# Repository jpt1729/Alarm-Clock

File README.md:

# Alarm-Clock

Custom built alarm clock. I was partly inspired by this https://busy.bar/. I also just wanted ot make a cool custom project and right now I only have an Alexa next to my bed so I can't actually see the current time, but with this it should both wake me up and it should tell me the time :) 

What this basically is its an ESP32 controlled alarm clock that connects to Wifi has a 1.9" LCD display and a snooze bar. It serves as a clock and an alarm (as of now, but I want to program it a bit more in the future!)

When I first learned about making PCBs this (along with a keyboard [which I already made!]) was one of the projects I wanted to try my hand at so I am happy I got to do it!

The plan to make the case a bit easier to print is to print the top part out and then the bottom part out and connect the two with a soldering iron. This will use a lot less plastic (if not I will basically be printing a solid block of plastic).

# Photos

# BOM

| Item | Quantity Used | Quantity Purchased | Designator | Part Number / Description | Link | Cost |
|------|--------------|-------------------|------------|--------------------------|------|------|
| Case | 1 | | | Custom Case | | |
| PCB | 1 | 5 | | Custom PCB | | $8.90 |
| JST Connector | 4 | 5 | | JST-XH-A 5 | [LCSC](https://lcsc.com/product-detail/Wire-To-Board-Connector_JST-B5B-XH-A-LF-SN_C157991.html) | $0.42 |
| JST Connector | 2 | 5 | | JST-XH-A 8 | [LCSC](https://lcsc.com/product-detail/Wire-To-Board-Connector_JST-B8B-XH-A-LF-SN_C157972.html) | $0.66 |
| MCU | 1 | 1 | | ESP-32-S3-MINI-1 | [LCSC](https://lcsc.com/product-detail/WiFi-Modules_Espressif-Systems-ESP32-S3-MINI-1-N8_C2913206.html) | $5.11 |
| Buzzer | 2 | 5 | | TMB12A05 | [LCSC](https://lcsc.com/product-detail/Buzzers_Jiangsu-Huaneng-Elec-TMB12A05_C96093.html) | $0.90 |
| Capacitor | 1 | 100 | C1 | 0603 1uF (100nF) | [LCSC](https://lcsc.com/product-detail/image/CC0603KRX7R9BB104_C14663.html) | $0.24 |
| USB Connector | 1 | 1 | J1 | USB-C USB4105-GF-A | [LCSC](https://lcsc.com/product-detail/USB-Connectors_Global-Connector-Technology-USB4105-GF-A_C3020560.html) | $1.16 |
| LCD Display | 1 | 10 | | 1.9" LCD | [AliExpress](https://www.aliexpress.us/item/3256807182983606.html) | $3.25 |
| Diodes | 2 | 10 | | 40V 200mA NPN TO-92 | [LCSC](https://lcsc.com/product-detail/image/2N3904X_C5156722.html) | $0.38 |
| Resistor | 1 | 100 | R1 | 10k Ohm 0603 | [LCSC](https://lcsc.com/product-detail/image/RC0603FR-0710KL_C98220.html) | $0.11 |
| Resistor | 2 | 100 | R2, R3 | 5.1k Ohm 0603 | [LCSC](https://lcsc.com/product-detail/image/RC0603FR-075K1L_C105580.html) | $0.12 |
| Resistor | 2 | 100 | R4, R5 | 1k Ohm 0603 | [LCSC](https://lcsc.com/product-detail/Chip-Resistor-Surface-Mount_YAGEO-RC0603FR-071KL_C22548.html) | $0.11 |
| Switch | 1 | 10 | SW1 | Gateron Low Profile | [AliExpress](https://www.aliexpress.us/item/3256808635477539.html) | $5.79 |
| Encoder | 1 | 5 | ENC1 | EC11 Rotary Encoder | [AliExpress](https://www.aliexpress.us/item/3256801237549169.html) | $0.99 |
| Voltage Regulator | 1 | 5 | U1 | AMS1117-3.3 | [LCSC](https://lcsc.com/product-detail/Voltage-Regulators-Linear-Low-Drop-Out-LDO-Regulators_Advanced-Monolithic-Systems-AMS1117-3-3_C6186.html) | $0.87 |
| SXH-001T-P0.6 | | 100 | | Terminal pin (x100) | [LCSC](https://lcsc.com/product-detail/Housing-Contact_JST-SXH-001T-P0-6_C140573.html) | $1.08 |
| XHP-5 | | 20 | | 5-pin housing (x20) | [LCSC](https://lcsc.com/product-detail/Housings-Wire-To-Board-Wire-To-Wire_JST-XHP-5_C144404.html) | $0.46 |
| XHP-8 | | 20 | | 8-pin housing (x20) | [LCSC](https://lcsc.com/product-detail/Housings-Wire-To-Board-Wire-To-Wire_JST-XHP-8_C144407.html) | $0.65 |
| Connector Kit (Amazon) | | | | SXH-001T-P0.6, XHP-5, XHP-8 Assortment | [Amazon](https://a.co/d/gTI01NR) | $6.97 |
| Shipping JLC PCB | | | | | | $22.73 |
| Shipping LCSC | | | | | | $17.39 |
| Shipping AliExpress | | | | | | $0.00 |
| Hotplate | 1 | 1 | | Soldering Hotplate | [AliExpress](https://www.aliexpress.us/item/3256806325004979.html) | $20.05 |
| **Total** | | | | | | **$77.72** |

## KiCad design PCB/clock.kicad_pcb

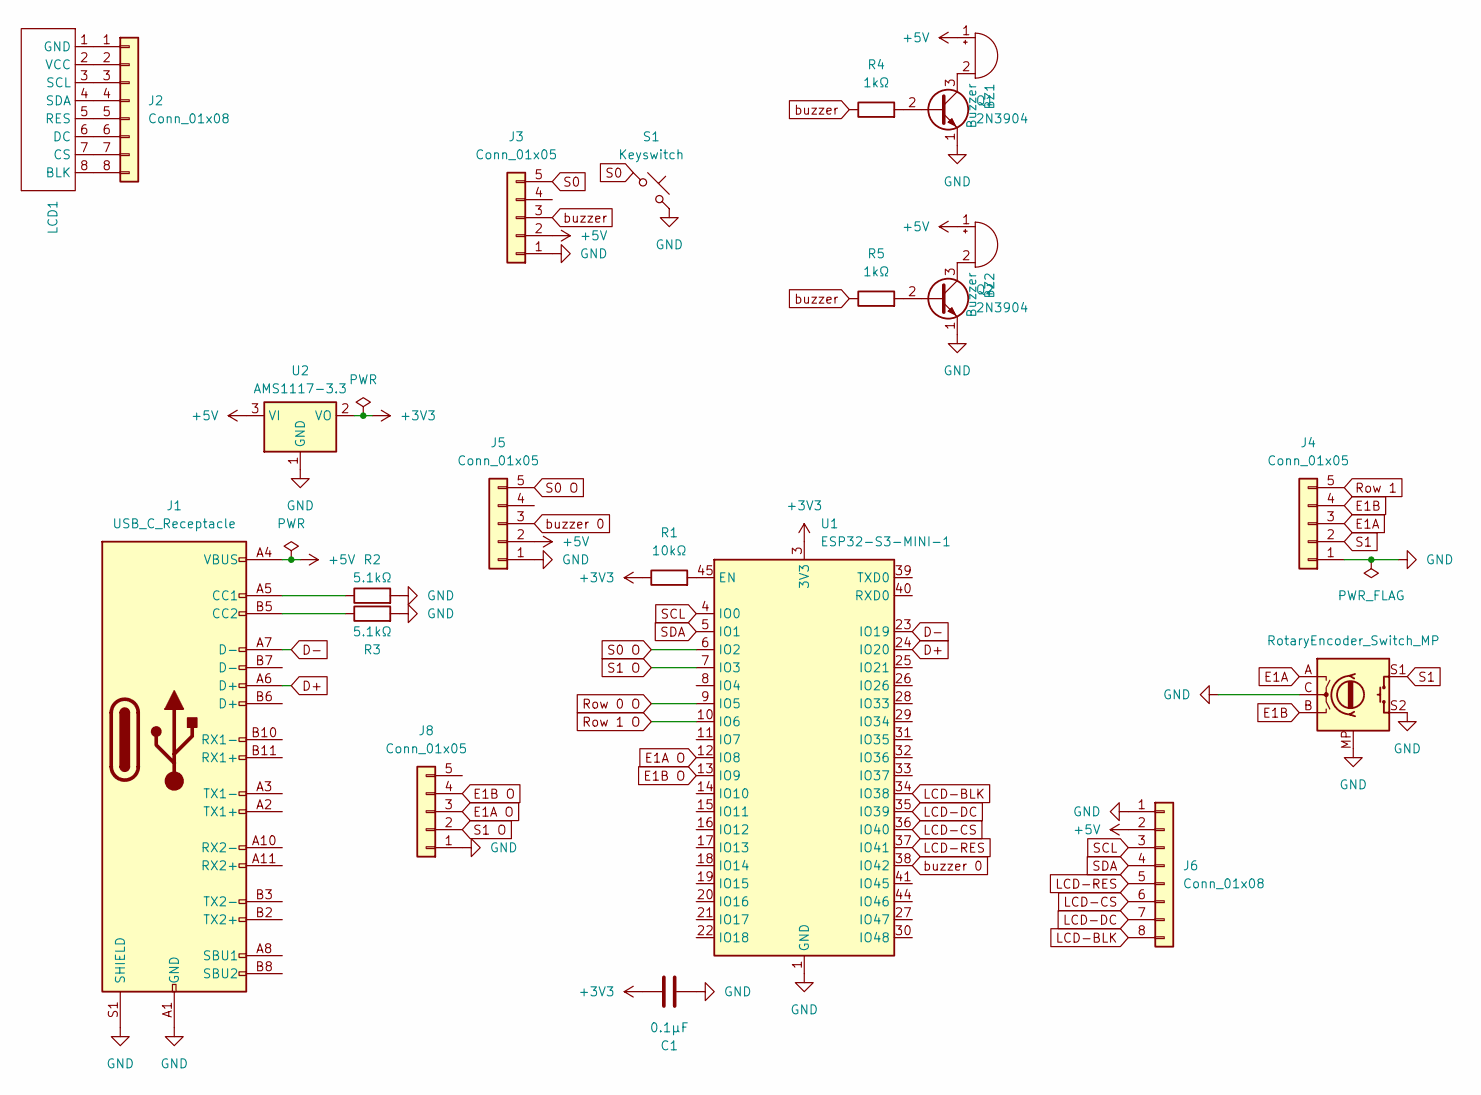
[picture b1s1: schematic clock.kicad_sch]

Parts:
BZ1, BZ2: Buzzer; Buzzer_12x9.5RM7.6
C1: 0.1µF; C_0603_1608Metric_Pad1.08x0.95mm_HandSolder
J1: USB_C_Receptacle; USB_C_Receptacle_GCT_USB4105-xx-A_16P_TopMnt_Horizontal
J2, J6: Conn_01x08; JST_XH_B8B-XH-A_1x08_P2.50mm_Vertical
J3, J4, J5, J8: Conn_01x05; JST_XH_B5B-XH-A_1x05_P2.50mm_Vertical
LCD1: TZT_1.9in_TFT_ST7789
Q1, Q2: 2N3904; TO-92_HandSolder
R1: 10kΩ; R_0603_1608Metric_Pad0.98x0.95mm_HandSolder
R2, R3: 5.1kΩ; R_0603_1608Metric_Pad0.98x0.95mm_HandSolder
R4, R5: 1kΩ; C_0603_1608Metric_Pad1.08x0.95mm_HandSolder
S1: Keyswitch; SW_KS33_1u
SW1: RotaryEncoder_Switch_MP; Encoder_EC11_MX
U1: ESP32-S3-MINI-1; ESP32-S2-MINI-1
U2: AMS1117-3.3; SOT-223-3_TabPin2

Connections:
+3V3: C1.2, R1.1, U1.3 (3V3), U2.2 (VO)
+5V: BZ1.1 (+), BZ2.1 (+), J1.A4 (VBUS), J1.A9 (VBUS), J1.B4 (VBUS), J1.B9 (VBUS), J3.2, J5.2, J6.2, U2.3 (VI)
D+: J1.A6 (D+), U1.24 (IO20)
D-: J1.A7 (D-), U1.23 (IO19)
E1A: J4.3, SW1.A
E1A O: J8.3, U1.12 (IO8)
E1B: J4.4, SW1.B
E1B O: J8.4, U1.13 (IO9)
GND: C1.1, J1.A1 (GND), J1.A12 (GND), J1.B1 (GND), J1.B12 (GND), J1.S1 (SHIELD), J3.1, J4.1, J5.1, J6.1, J8.1, Q1.1 (E), Q2.1 (E), R2.2, R3.2, S1.2, SW1.C, SW1.MP, SW1.S2, U1.1 (GND), U1.2 (GND), U1.42 (GND), U1.43 (GND), U1.46 (GND), U1.47 (GND), U1.48 (GND), U1.49 (GND), U1.50 (GND), U1.51 (GND), U1.52 (GND), U1.53 (GND), U1.54 (GND), U1.55 (GND), U1.56 (GND), U1.57 (GND), U1.58 (GND), U1.59 (GND), U1.60 (GND), U1.61 (GND), U1.62 (GND), U1.63 (GND), U1.64 (GND), U1.65 (GND), U2.1 (GND)
LCD-BLK: J6.8, U1.34 (IO38)
LCD-CS: J6.6, U1.36 (IO40)
LCD-DC: J6.7, U1.35 (IO39)
LCD-RES: J6.5, U1.37 (IO41)
unnamed: BZ1.2 (-), Q1.3 (C)
unnamed: BZ2.2 (-), Q2.3 (C)
unnamed: J1.A5 (CC1), R2.1
unnamed: J1.B5 (CC2), R3.1
unnamed: J2.1, LCD1.1 (GND)
unnamed: J2.2, LCD1.2 (VCC)
unnamed: J2.3, LCD1.3 (SCL)
unnamed: J2.4, LCD1.4 (SDA)
unnamed: J2.5, LCD1.5 (RES)
unnamed: J2.6, LCD1.6 (DC)
unnamed: J2.7, LCD1.7 (CS)
unnamed: J2.8, LCD1.8 (BLK)
unnamed: Q1.2 (B), R4.2
unnamed: Q2.2 (B), R5.2
unnamed: R1.2, U1.45 (EN)
Row 0 O: U1.9 (IO5)
Row 1: J4.5
Row 1 O: U1.10 (IO6)
S0: J3.5, S1.1
S0 O: J5.5, U1.6 (IO2)
S1: J4.2, SW1.S1
S1 O: J8.2, U1.7 (IO3)
SCL: J6.3, U1.4 (IO0)
SDA: J6.4, U1.5 (IO1)
buzzer: J3.3, R4.1, R5.1
buzzer 0: J5.3, U1.38 (IO42)

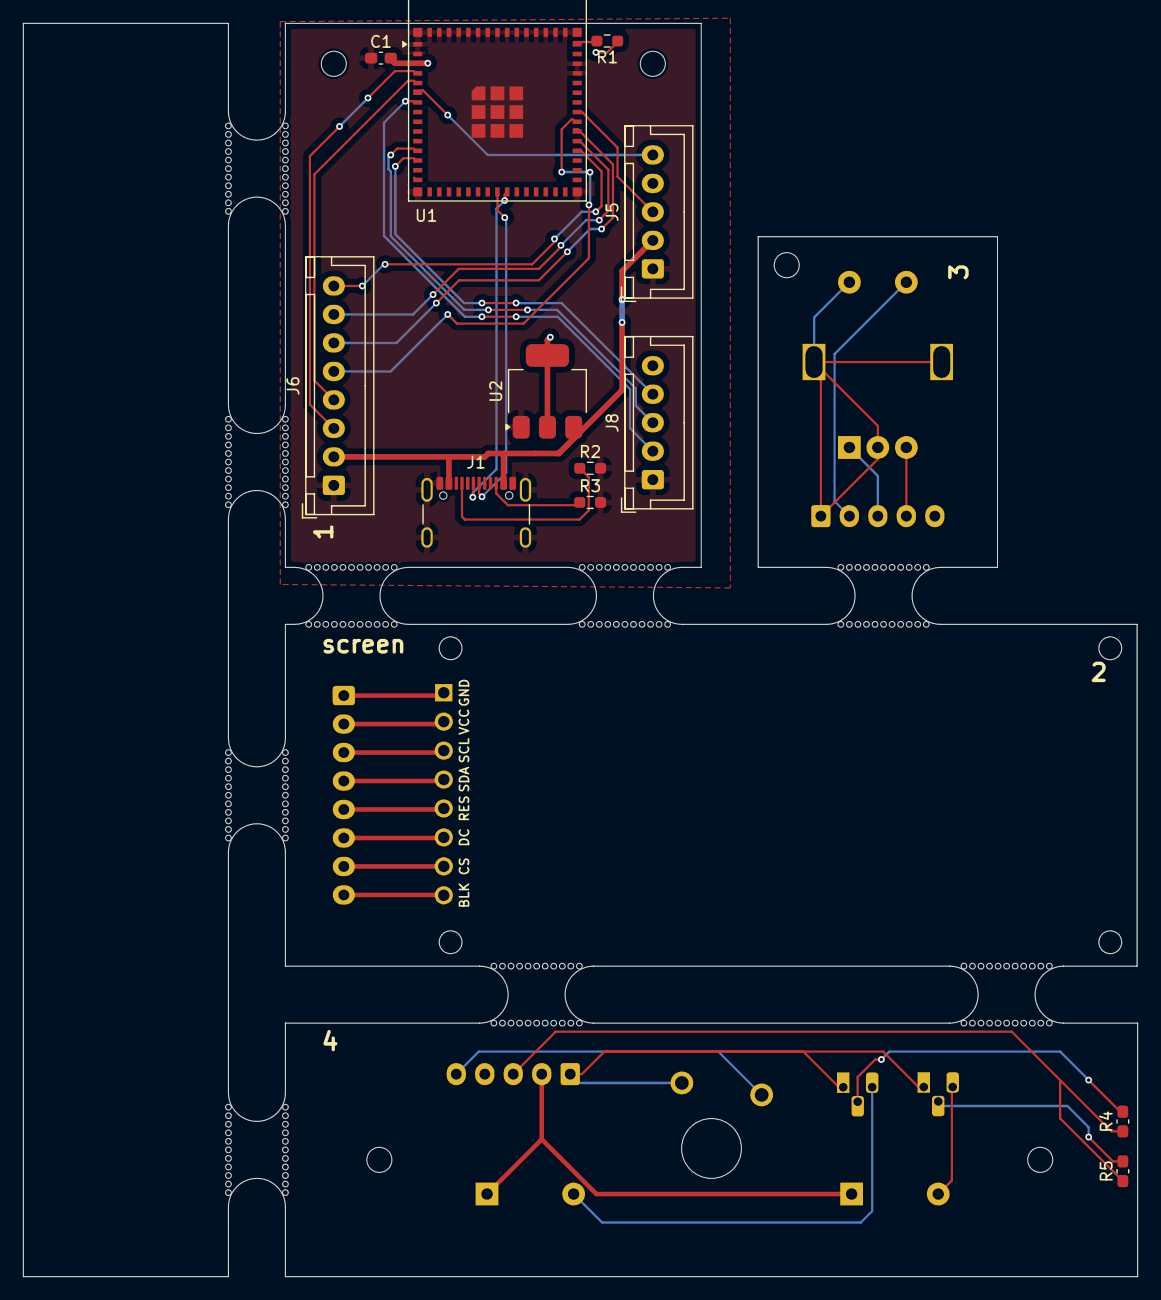
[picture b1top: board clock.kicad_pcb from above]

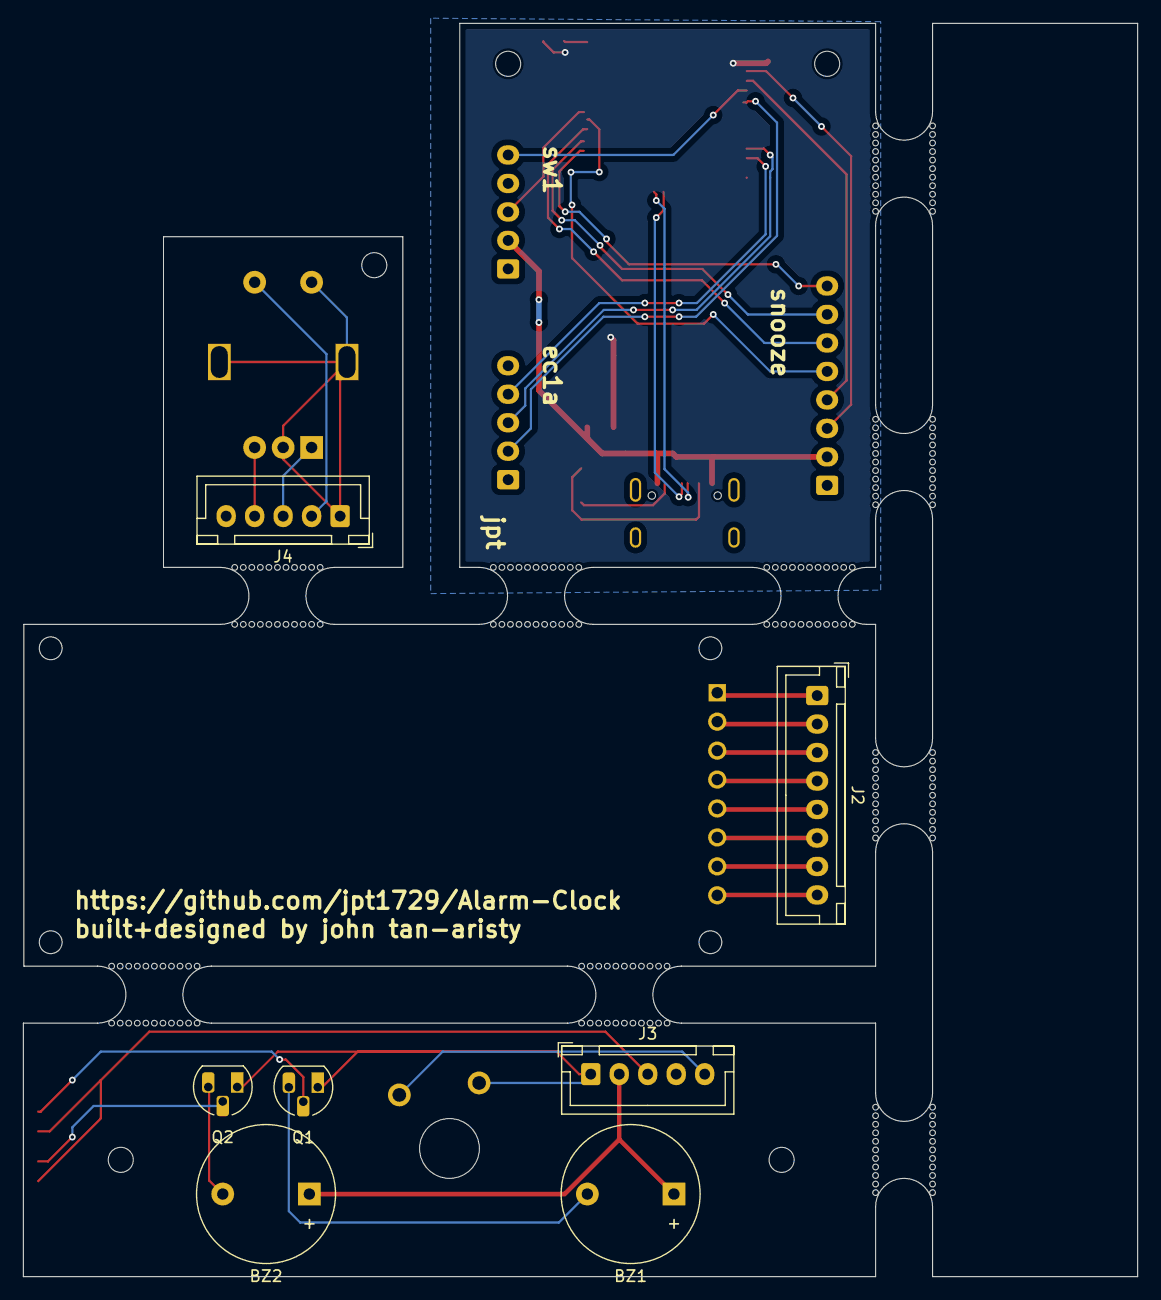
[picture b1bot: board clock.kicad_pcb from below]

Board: 2 copper layers, 97.8 x 110.0 mm, 31 parts (7 on the bottom side), 36 nets.

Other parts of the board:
mouse-bite-5mm-slot, mouse-bite-5mm-slot#2, mouse-bite-5mm-slot#3, mouse-bite-5mm-slot#4, mouse-bite-5mm-slot#5, mouse-bite-5mm-slot#6, mouse-bite-5mm-slot#7, mouse-bite-5mm-slot#8, mouse-bite-5mm-slot#9: VAL**; mouse-bite-5mm-slot

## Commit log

2025-06-29 Rename Screenshot 2025-06-29 170308.png to schematic-6-29-2025
2025-06-29 Rename schematic-6-29-2025 to schematic-6-29-2025.png
2025-07-01 photos + case + journal entry
2025-07-01 ready to submit?
2025-07-01 pcb remove hotswap switch
2025-07-02 fixes
2025-07-24 pannelization
2025-07-24 readme
2025-07-24 hotplate
